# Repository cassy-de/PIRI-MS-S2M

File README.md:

# PIRI-MS-S2M
PIRI-MS-S2M: Multisensor-Transmitter, basierend auf den beiden Funkprotokollen FS20 und FHT.

Der Passiv-Infrarotsensor detektiert Bewegungen und schickt diese via FS20 an die Zentrale oder Appliances, während die Messwerte der Temperatur und Luftfeuchtigkeit mittels FHT-Funkprotokoll an das Hausautomationsnetzwerk FHEM übermittelt werden. 

------------------

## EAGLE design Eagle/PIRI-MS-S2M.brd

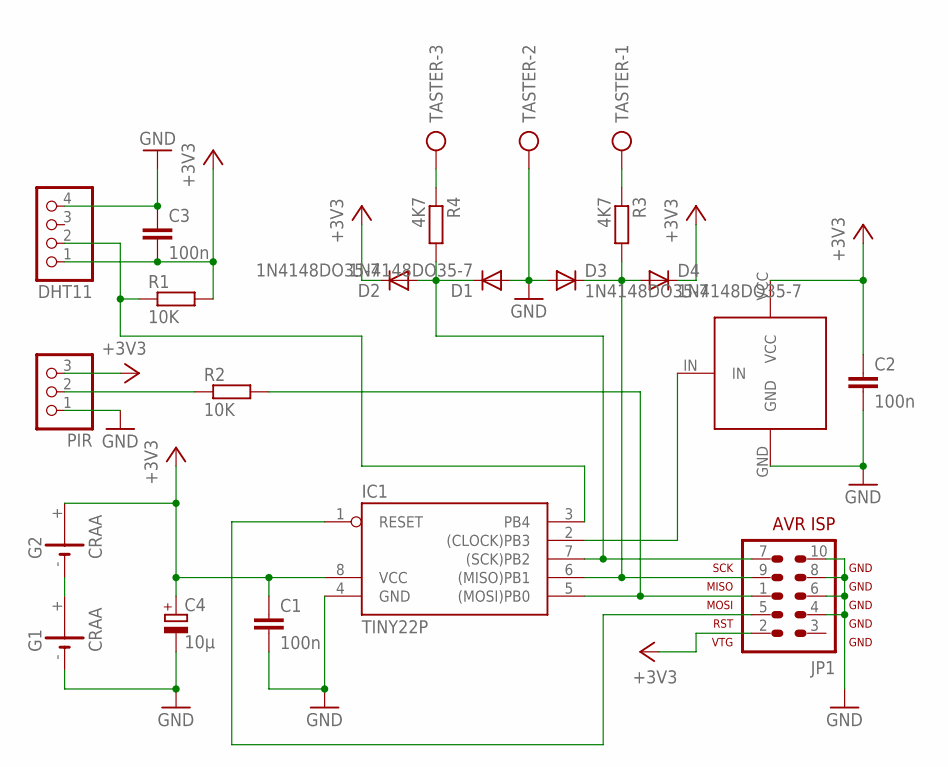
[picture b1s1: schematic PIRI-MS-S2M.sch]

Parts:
C1, C2, C3: 100n; C050-024X044
C4: 10µ; E5-4
D1, D2, D3, D4: 1N4148DO35-7; DO35-7
DHT11: PINHD-1X4; 1X04
G1, G2: CRAA
IC1: TINY22P; DIL08
JP1: AVR-ISP-10
PIR: PINHD-1X3; 1X03
R1, R2: 10K; 0204/7
R3, R4: 4K7; 0204/7
TASTER: AK500/3
U$1: TX868

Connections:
+3V3: C1.1, C2.1, C3.2, C4.+, D2.C, D4.C, DHT11.1, G2.+, IC1.8 (VCC), JP1.2, PIR.3, R1.2, U$1.VCC
GND: C1.2, C2.2, C3.1, C4.-, D1.A, D3.A, DHT11.4, G1.-, IC1.4 (GND), JP1.4, JP1.6, JP1.8, JP1.10, PIR.1, TASTER.2, U$1.GND
unnamed: IC1.1 (RESET), JP1.5
unnamed: IC1.5 ((MOSI)PB0), JP1.1, R2.2
unnamed: D3.C, D4.A, IC1.6 ((MISO)PB1), JP1.9, R3.2
unnamed: D1.C, D2.A, IC1.7 ((SCK)PB2), JP1.7, R4.2
unnamed: PIR.2, R2.1
unnamed: R4.1, TASTER.3
unnamed: IC1.2 ((CLOCK)PB3), U$1.IN
unnamed: DHT11.2, IC1.3 (PB4), R1.1
unnamed: R3.1, TASTER.1
unnamed: G1.+, G2.-

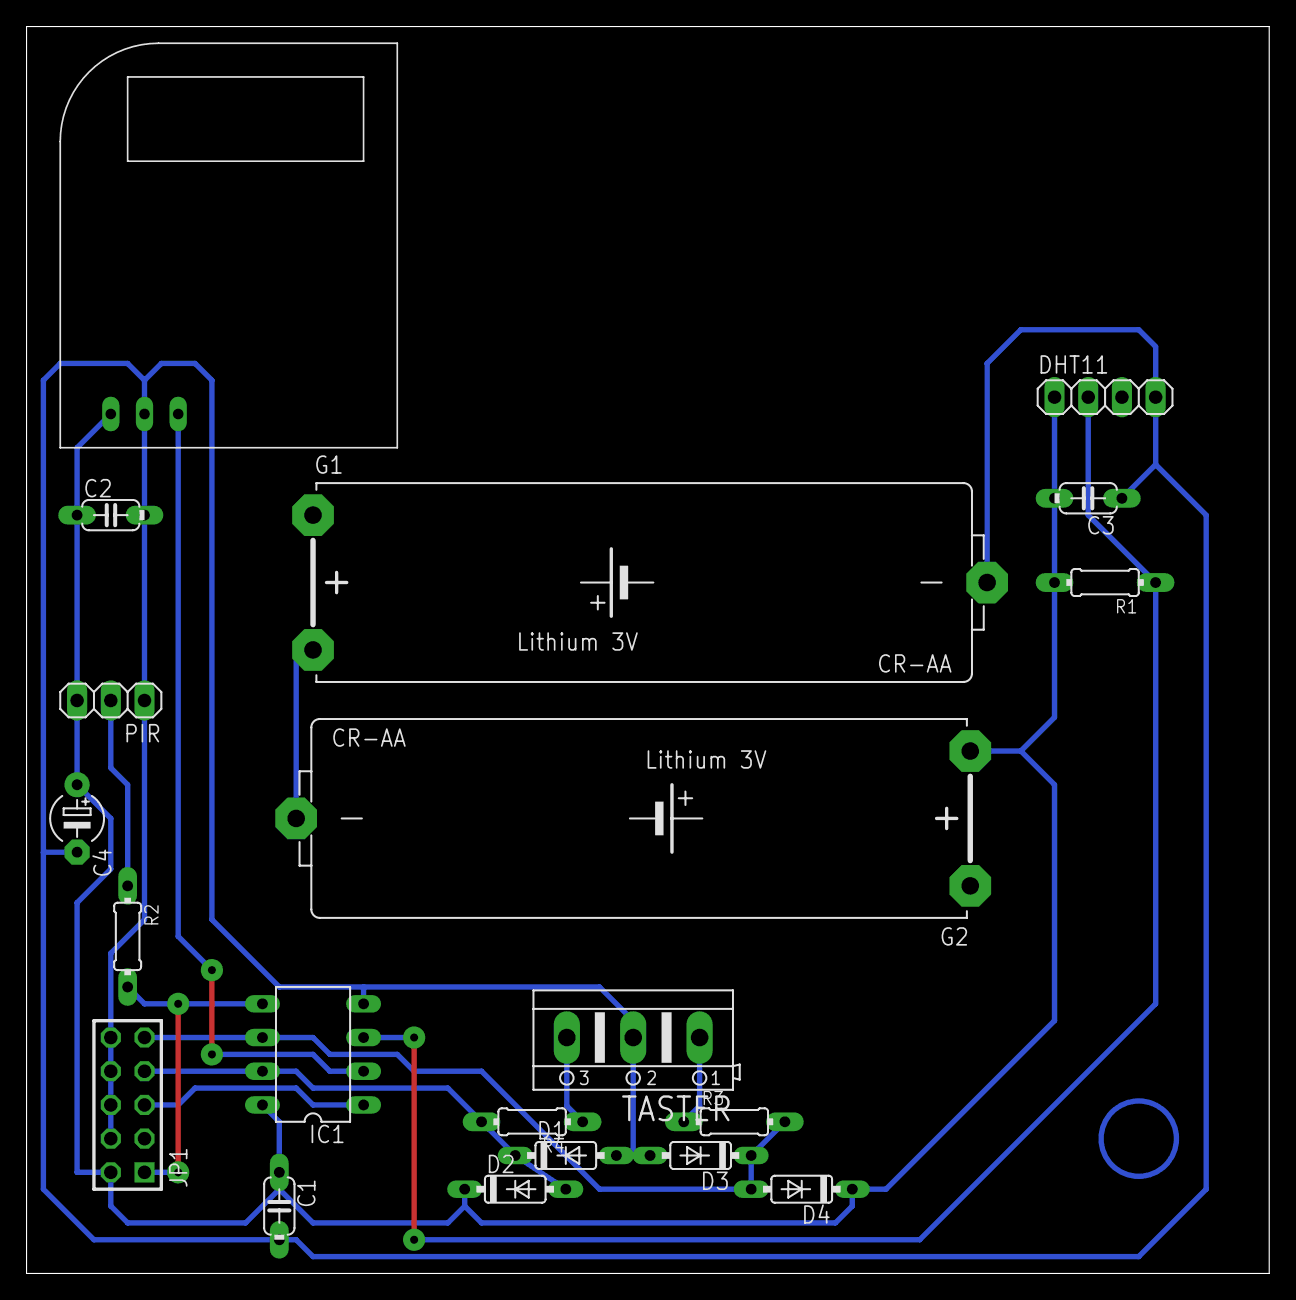
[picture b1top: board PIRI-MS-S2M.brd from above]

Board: 2 copper layers, 93.7 x 94.0 mm, 20 parts (0 on the bottom side), 12 nets.

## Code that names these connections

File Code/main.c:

/*  PIRI-MS-S2M    [ Passiv-Infrarot-Innen--MultiSensor-Sende-2fach-Modul ]
*                  [  Budget-Version mit DHT11 Temperatur / Luftfeuche    ]
*                  [ PIR OHNE Helligkeitserkennung -> Präsenzmelder/Alarm ]
*                  [ Author: Christoph-A. Straessle <cassy>  2014         ]
************************************************************************
* ATiny 25 intern 8Mhz Takt DIV8 -> 1MHz
* WDTON Fuse darf nicht gesetzt sein -> fuses.sh
*     HARDWARE und KONSTANTEN, siehe definitus.h
* PB0/SDA PCINT0 <- IN fuer PIR      -> fs20_adr0 
* PB1     PCINT1 <- IN fuer Taster 1 -> fs20_adr1 kurz=EIN / lang=AUS
* PB2/SCL PCINT2 <- IN fuer Taster 2 -> fs20_adr2 kurz=EIN / lang=AUS
* PB3 OUT FS20 Senden an TX868 (high-active) bei Tastendruck / PIR
* PB3 OUT KS300 Senden an TX868 (high-active)
* PB4 IN/OUT DHT11 mit 10k-Pullup an 3V
************************************************************************
*/
#include <avr/io.h>
#include <avr/sleep.h>
#include <avr/interrupt.h>
#include <util/delay.h>
#include "definitus.h" 
// Includes im Verzeichnis clib/
#include "fs20.c"
#include "s300.c"
#include "dht.c"

// Deklarationen fuer S300-BCD-Werte
volatile uint8_t  s300_sign = 0;	// Temperatur Vorzeichen 0=pos 1=neg
volatile uint8_t  s300_t001 = 0;	// Temperatur Zehntel
volatile uint8_t  s300_t010 = 0;	// Temperatur Einer
volatile uint8_t  s300_t100 = 0;	// Temperatur Zehner
volatile uint8_t  s300_h001 = 0;	// Feuchtigkeit Zehntel
volatile uint8_t  s300_h010 = 0;	// Feuchtigkeit Einer
volatile uint8_t  s300_h100 = 0;	// Feuchtigkeit Zehner
// Deklarationen fuer DHT11-Abfragen
          int8_t  s300_temp = 0;
          int8_t  s300_hum  = 0;
          int8_t  rval = 0;		// Rueckgabewert fuer Subs
// Counter und Statusvariablen
volatile uint8_t  xmt_cnt = 0;	// Sendezaehler 
volatile uint8_t  pir_re = 0;	// PIR rising edge
volatile uint8_t  ta1_fe = 0;	// Taster1 falling edge
volatile uint8_t  ta2_fe = 0;	// Taster2 falling edge

// ## IRQ ##################################################################

// PIR- und Tasten-ISR
ISR( PCINT0_vect )
{
  GIMSK = 0;			// globale Sperre zum Schutz vor IRQ-Flutung
  if (PINB & (1<<PIR))
    { pir_re=1; }   		// rising edge am PIR-Eingang -> Flag setzen
  if ( !(PINB & (1<<TA1)) )
    { ta1_fe=1; }   		// falling edge am TA1-Eingang -> Flag setzen
  if ( !(PINB & (1<<TA2)) )
    { ta2_fe=1; }   		// falling edge am TA2-Eingang -> Flag setzen
} // of ISR Pin-Change-IRQ


// Watchdog ISR
ISR(WDT_vect) 
{
  xmt_cnt++;		// alle 8 sec um 1 erhoehen
} // of ISR Watchdog

// ## MAIN #################################################################
 
int main (void) {
  FS20_DDR |= (1 << FS20_PORTPIN);	 	// FS20-Portpin OUT und LOW 
  FS20_PORT &= ~(1 << FS20_PORTPIN);

  PORTB |= (1<<TA1) | (1<<TA2);			// Taster Pull-Ups  

  MCUSR |= (1 << WDRF);  			// WDT ein
  WDTCR |= (1 << WDIE) | (1 << WDP3) | (1 << WDP0); //WDT Interrupt ein
						// Timer Prescaler 1024-> 8.0s
  ACSR = (1<<ACD);				// Analog Comparator aus
  PCMSK = (1<<PIR) | (1<<TA1) | (1<<TA2);	// select pin change IRQ
  sei();					// IRQ freigegeben
 
  for(;;)
  {
   GIMSK = 1<<PCIE;				// Awake Interrupt ein 
   set_sleep_mode(SLEEP_MODE_PWR_DOWN);  
   // sleep_mode();
   sleep_cpu(); 				// ... und schlafen zZzZzZzZzZz
 
   // hier wachen wir wieder auf
    if (xmt_cnt > (20 + s300_adr) )		// Variation der Sendezeiten
    {						//  in Abhaengigkeit der S300Nr
      // nun sind rund 2-4 Min vergangen, sende S300TH-Daten
      xmt_cnt = 0;
      s300_t100 = 0;		// Alle BCD-Variablen auf "0" setzen
      s300_t010 = 0;		//  somit kann ein DHT-Ausfall an
      s300_h100 = 0;		//  konstant gesendeten 00,0 C
      s300_h010 = 0;		//  und 00,0 rF erkannt werden

      if(dht_gettemperaturehumidity(&s300_temp, &s300_hum) != -1) 
      {
	s300_t100 = s300_temp / 10;
	s300_t010 = s300_temp - ( s300_t100 * 10 );
	s300_t001 = 0;		// keine Nachkommastelle

  	s300_h100 = s300_hum / 10;
	s300_h010 = s300_hum - ( s300_h100 * 10 );
	s300_h001 = 0;		// keine Nachkommastelle
      } // of if dht...

      s300_send(s300_adr, s300_sign, s300_t001, s300_t010, s300_t100,
			 s300_h001, s300_h010, s300_h100);
    } 		    // of if xmt_cnt


    if (pir_re == 1)		// PIR, ohne Entprell-Logik, da Monoflop
    {				//  Monoflopzeit > 30 S waehlen (Poti)
      pir_re = 0;		// PIR hat getriggert, Flag zuruecksetzen
      fs20_send(fs20_fht, fs20_hc, fs20_adr0, fs20_cOFT, fs20_cOFT2);
    } // of if pir_re


    if (ta1_fe == 1)		// Taster 1 gedrueckt
    _delay_ms(100);		// Entprellzeit abwarten
    { 
      if ( !(PINB & (1<<TA1)) )	// ist der PIN noch LOW?
        {
          _delay_ms(200);
          _delay_ms(200);	// 0,5 S insgesamt
          if ( !(PINB & (1<<TA1)) )	// PIN immer noch LOW?-> lang -> AUS
          {
            fs20_send(fs20_fht, fs20_hc, fs20_adr1, fs20_cmd12, fs20_cmd12b);
          }
          else				// kurzer Tastendruck -> EIN
          {
            fs20_send(fs20_fht, fs20_hc, fs20_adr1, fs20_cmd1, fs20_cmd1b);
          }
        }
      ta1_fe=0; 
    } // of TA1-Eingang


    if (ta2_fe == 1)		// Taster 2 gedrueckt
    _delay_ms(100);		// Entprellzeit abwarten
    { 
      if ( !(PINB & (1<<TA2)) )	// ist der PIN noch LOW?
        {
          _delay_ms(200);
          _delay_ms(200);	// 0,5 S insgesamt
          if ( !(PINB & (1<<TA2)) )	// PIN immer noch LOW?-> lang -> AUS
          {
            fs20_send(fs20_fht, fs20_hc, fs20_adr1, fs20_cmd22, fs20_cmd22b);
          }
          else				// kurzer Tastendruck -> EIN
          {
            fs20_send(fs20_fht, fs20_hc, fs20_adr1, fs20_cmd2, fs20_cmd2b);
          }
        }
      ta2_fe=0; 
    } // of TA2-Eingang


    // Return to sleep
  } 		  // of for(ewer)
} 		// of main
